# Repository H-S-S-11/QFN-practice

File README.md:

# QFN-practice
A basic PCB with three sizes of QFN MCU for practicing fine soldering

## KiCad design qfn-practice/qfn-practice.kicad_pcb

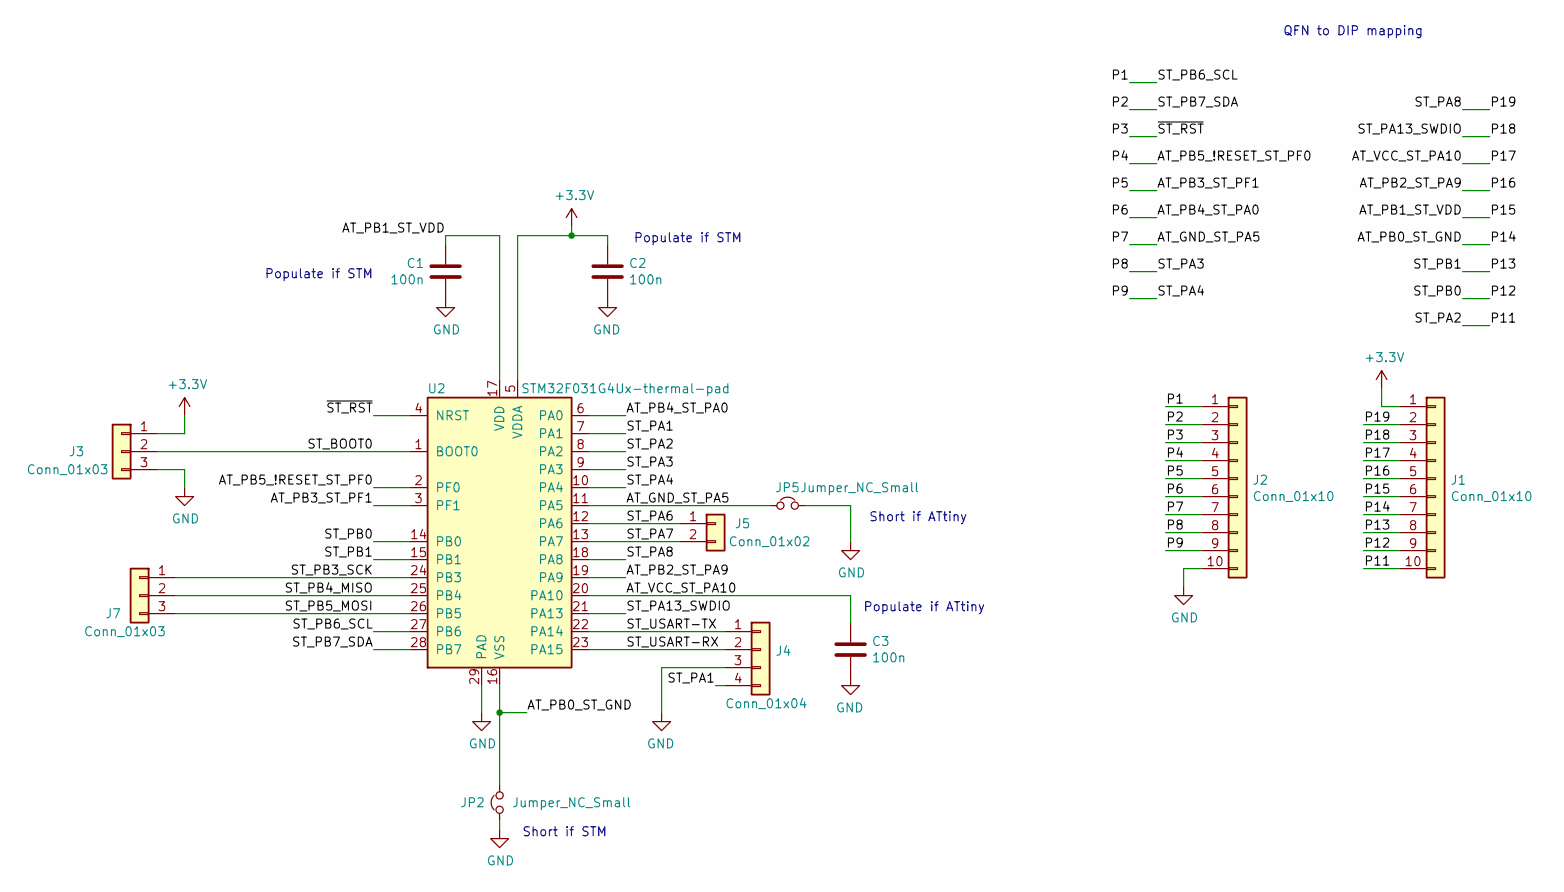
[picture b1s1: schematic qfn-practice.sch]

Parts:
C1, C2, C3: 100n; RC-1206-0805-hybrid
J1, J2: Conn_01x10; PinHeader_1x10_P2.54mm_Vertical
J3, J7: Conn_01x03; PinHeader_1x03_P2.54mm_Vertical
J4: Conn_01x04; PinHeader_2x02_P2.54mm_Vertical
J5: Conn_01x02; PinHeader_1x02_P2.54mm_Vertical
JP2, JP5: Jumper_NC_Small; 0202-solder-jumper
U2: STM32F031G4Ux-thermal-pad; QFN28-4x4mm-0_5mmP-thermalpad

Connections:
+3V3: C2.2, J1.1, J3.1, U2.5 (VDDA)
/AT_GND_ST_PA5: J2.7, JP5.1, U2.11 (PA5)
/AT_PB0_ST_GND: J1.7, JP2.2, U2.16 (VSS)
/AT_PB1_ST_VDD: C1.2, J1.6, U2.17 (VDD)
/AT_PB2_ST_PA9: J1.5, U2.19 (PA9)
/AT_PB3_ST_PF1: J2.5, U2.3 (PF1)
/AT_PB4_ST_PA0: J2.6, U2.6 (PA0)
/AT_PB5_!RESET_ST_PF0: J2.4, U2.2 (PF0)
/AT_VCC_ST_PA10: C3.2, J1.4, U2.20 (PA10)
/P1: J2.1, U2.27 (PB6)
/P2: J2.2, U2.28 (PB7)
/P3: J2.3, U2.4 (NRST)
/P8: J2.8, U2.9 (PA3)
/P9: J2.9, U2.10 (PA4)
/P11: J1.10, U2.8 (PA2)
/P12: J1.9, U2.14 (PB0)
/P13: J1.8, U2.15 (PB1)
/P18: J1.3, U2.21 (PA13)
/P19: J1.2, U2.18 (PA8)
/ST_BOOT0: J3.2, U2.1 (BOOT0)
/ST_PA1: J4.4, U2.7 (PA1)
/ST_PA6: J5.1, U2.12 (PA6)
/ST_PA7: J5.2, U2.13 (PA7)
/ST_PB3_SCK: J7.1, U2.24 (PB3)
/ST_PB4_MISO: J7.2, U2.25 (PB4)
/ST_PB5_MOSI: J7.3, U2.26 (PB5)
/ST_USART-RX: J4.2, U2.23 (PA15)
/ST_USART-TX: J4.1, U2.22 (PA14)
GND: C1.1, C2.1, C3.1, J2.10, J3.3, J4.3, JP2.1, JP5.2, U2.29 (PAD)

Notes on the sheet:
Populate if ATtiny
Populate if STM
Populate if STM
Short if STM
Short if ATtiny
QFN to DIP mapping

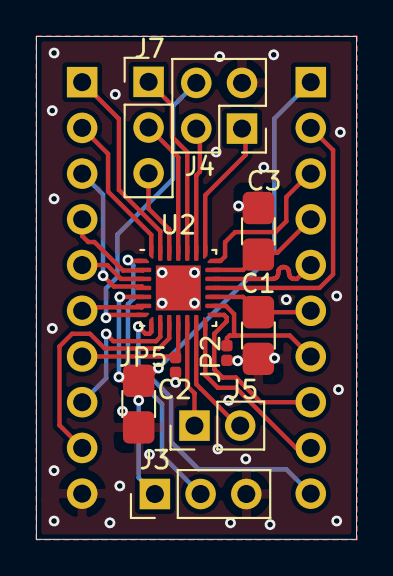
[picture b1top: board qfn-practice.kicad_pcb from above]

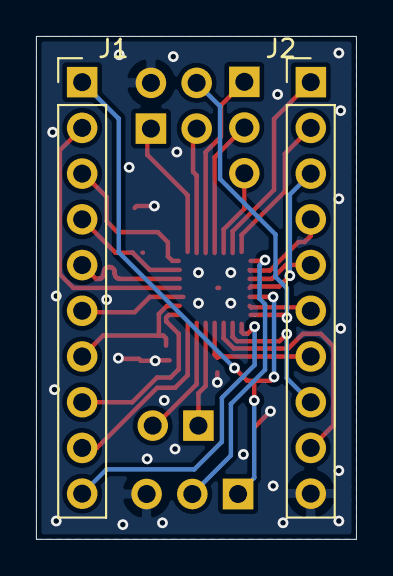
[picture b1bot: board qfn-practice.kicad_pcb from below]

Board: 4 copper layers, 17.8 x 27.9 mm, 12 parts (2 on the bottom side), 29 nets.

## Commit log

2021-03-09 start PCB
2021-03-20 map attiny pins to stm32 footprint
2021-03-20 route to all side pins
2021-03-20 remove pdfs
2021-03-30 add headers for programming etc
2021-03-31 complete first draft
2021-03-31 tune track lengths for possible USB pair
2021-03-31 shuffle things around
2021-04-14 add gitignore
2021-05-03 ground lines
2021-05-03 remove junk
2021-05-03 add kicad template gitignore
2021-05-26 small tweaks
2021-06-06 add 2 layer gerbers
2021-06-06 4 layer gerbers
